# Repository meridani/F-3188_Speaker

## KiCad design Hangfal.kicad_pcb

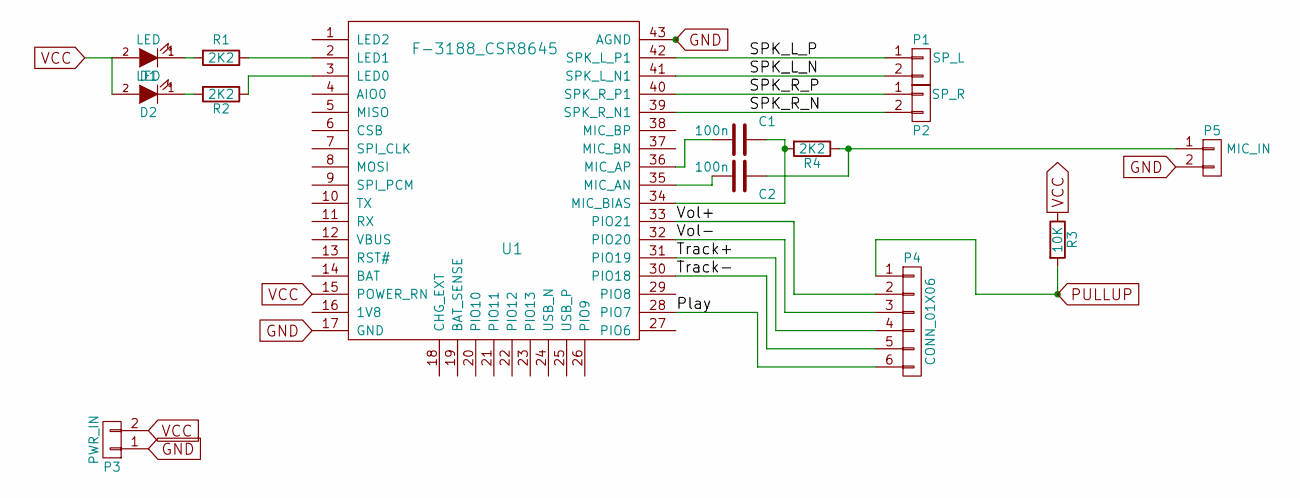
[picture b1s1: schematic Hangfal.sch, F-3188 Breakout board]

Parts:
C1, C2: 100n; C_Disc_D3_P2.5
D1, D2: LED; LED-3MM
P1: SP_L; mors_2p
P2: SP_R; mors_2p
P3: PWR_IN; mors_2p
P4: CONN_01X06; Pin_Header_Straight_1x06
P5: MIC_IN; Pin_Header_Straight_1x02
R1, R2, R4: 2K2; Resistor_Horizontal_RM7mm
R3: 10K; Resistor_Horizontal_RM7mm
U1: F-3188_CSR8645; f3188_CSR8645

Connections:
/Play: P4.6, U1.28 (PIO7)
/SPK_L_N: P1.2, U1.41 (SPK_L_N1)
/SPK_L_P: P1.1, U1.42 (SPK_L_P1)
/SPK_R_N: P2.2, U1.39 (SPK_R_N1)
/SPK_R_P: P2.1, U1.40 (SPK_R_P1)
/Track+: P4.4, U1.31 (PIO19)
/Track-: P4.5, U1.30 (PIO18)
/Vol+: P4.2, U1.33 (PIO21)
/Vol-: P4.3, U1.32 (PIO20)
GND: P3.1, P5.2, U1.17 (GND), U1.43 (AGND)
unnamed: C1.1, R4.2, U1.34 (MIC_BIAS)
unnamed: C1.2, U1.36 (MIC_AP)
unnamed: C2.1, P5.1, R4.1
unnamed: C2.2, U1.35 (MIC_AN)
unnamed: D1.1 (K), R1.2
unnamed: D2.1 (K), R2.2
unnamed: R1.1, U1.2 (LED1)
unnamed: R2.1, U1.3 (LED0)
PULLUP: P4.1, R3.2
VCC: D1.2 (A), D2.2 (A), P3.2, R3.1, U1.15 (POWER_RN)

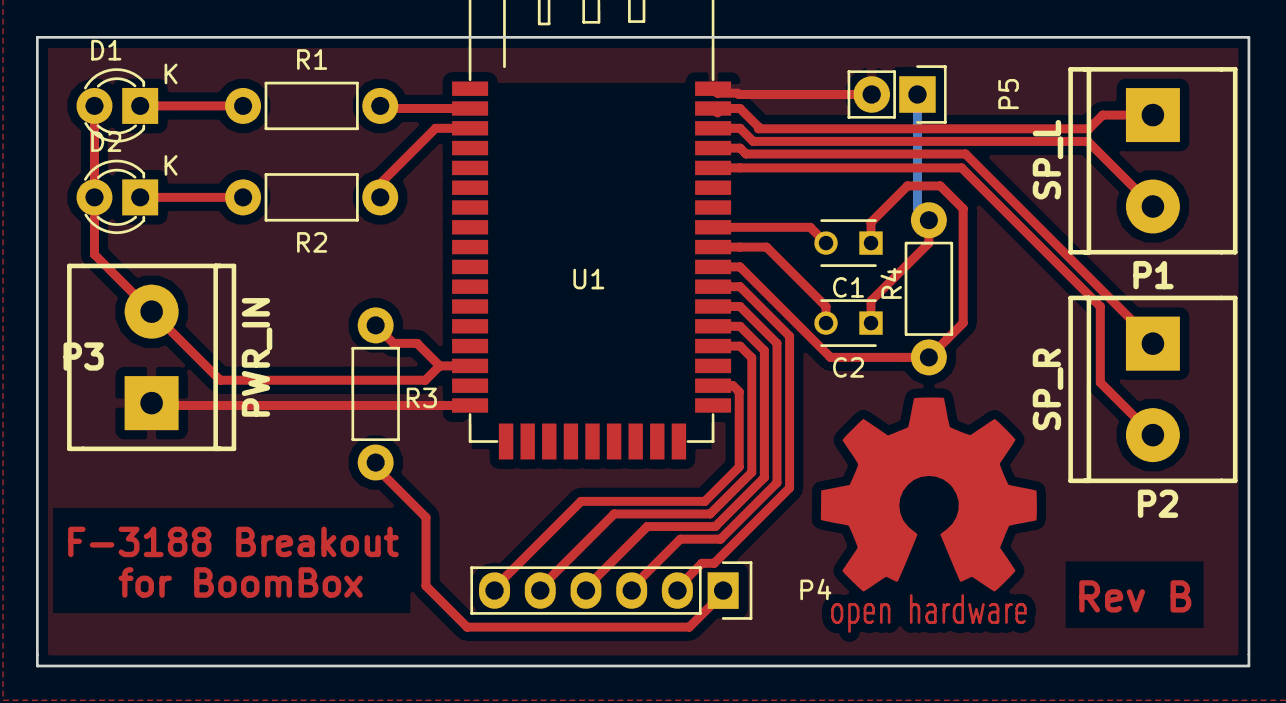
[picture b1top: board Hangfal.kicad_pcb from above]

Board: 2 copper layers, 67.3 x 34.9 mm, 14 parts (0 on the bottom side), 20 nets.

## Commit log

2016-06-07 Added SVG
